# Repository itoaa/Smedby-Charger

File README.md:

Smedby-Charger
==============

Arduino based battery charger

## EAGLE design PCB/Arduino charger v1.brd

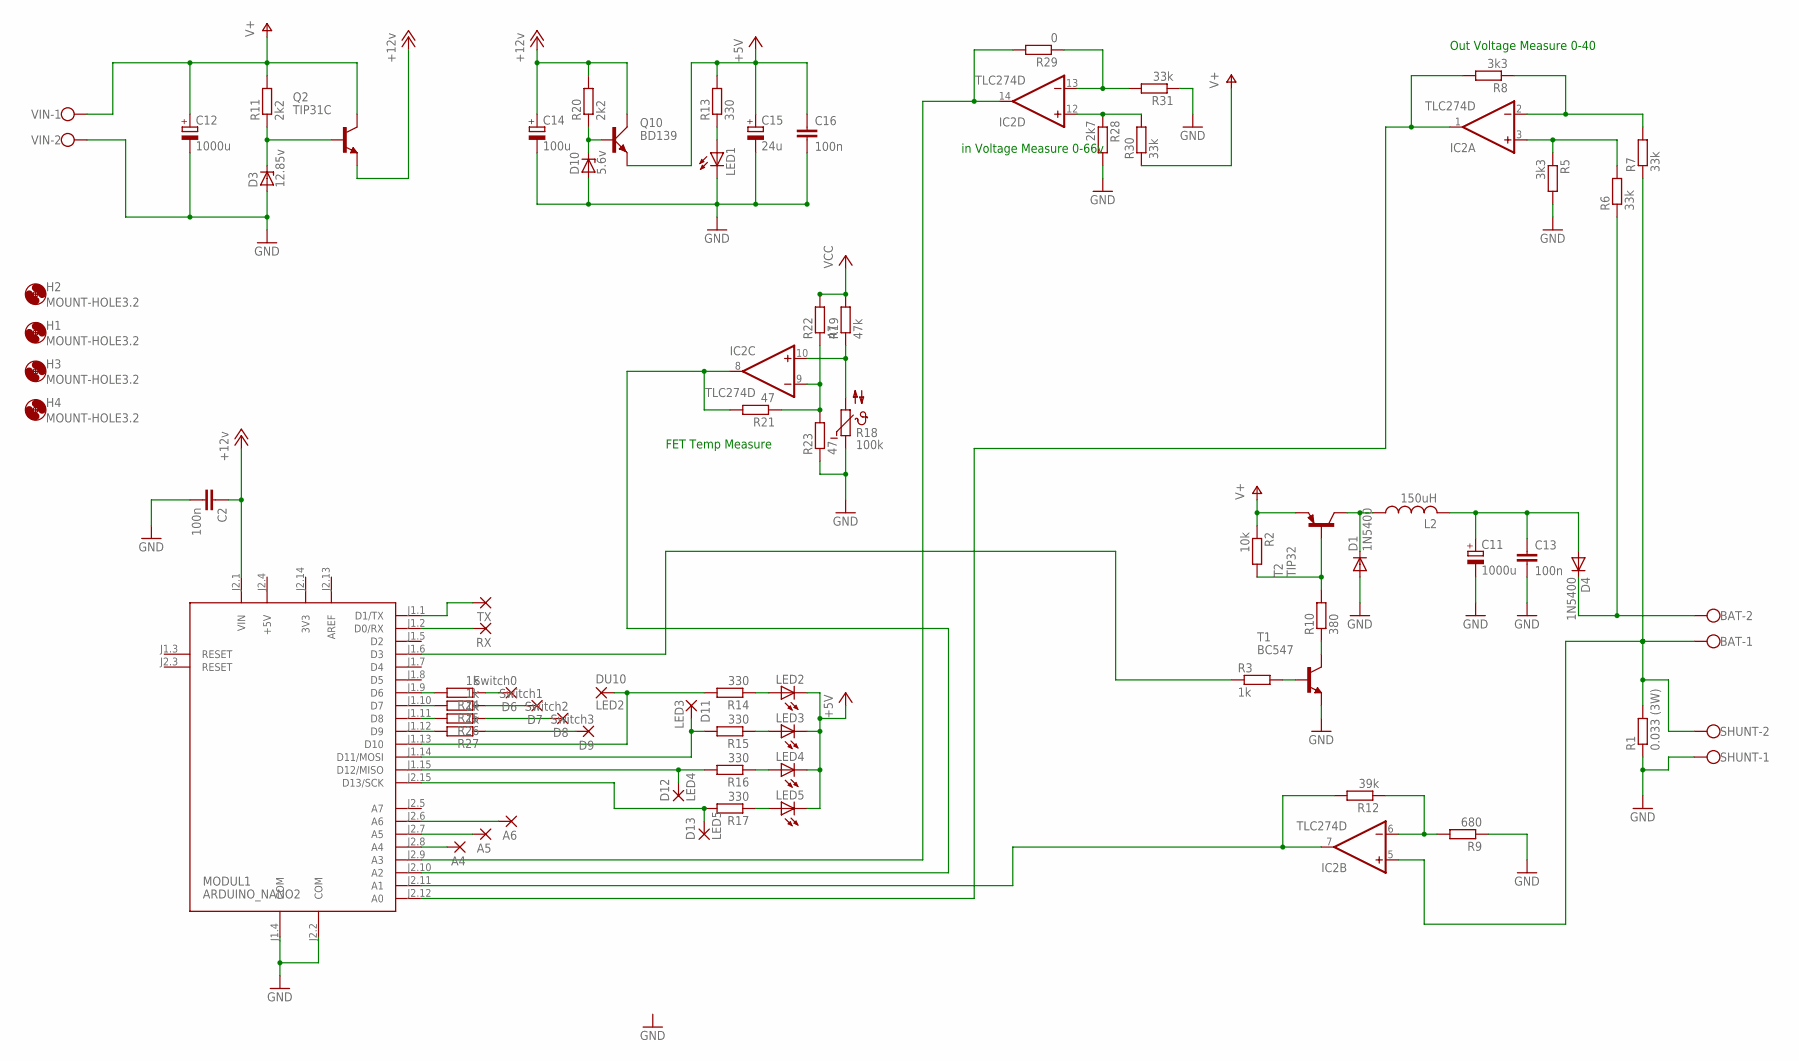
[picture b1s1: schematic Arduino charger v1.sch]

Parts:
A4, A5, A6: 1,6/0,9
BAT: W237-102
C2, C13, C16: 100n; C050-024X044
C11, C12: 1000u; E7,5-18
C14: 100u; E2,5-5
C15: 24u; E2,5-5
D1, D4: 1N5400; DO201-15
D3: 12.85v; DO35Z10
D6: Switch0; 1,6/0,9
D7: Switch1; 1,6/0,9
D8: Switch2; 1,6/0,9
D9: Switch3; 1,6/0,9
D10: 5.6v; DO35Z10
D11: LED3; 1,6/0,9
D12: LED4; 1,6/0,9
D13: LED5; 1,6/0,9
DU10: LED2; 1,6/0,9
H1, H2, H3, H4: MOUNT-HOLE3.2; 3,2
IC2: TLC274D; SO14
L2: 150uH; TJ4-U1
LED1, LED2, LED3, LED4, LED5: LED3MM
MODUL1: ARDUINO_NANO2
Q2: TIP31C; TO220
Q10: BD139; TO126AV
R1: 0.033 (3W); 0922/22
R2: 10k; 0207/2V
R3, R24, R25, R26, R27: 1k; 0207/2V
R5, R8: 3k3; 0207/2V
R6, R7, R30, R31: 33k; 0207/2V
R9: 680; 0207/2V
R10: 380; P0613V
R11: 2k2; 0617/17
R12: 39k; 0207/2V
R13, R14, R15, R16, R17: 330; 0207/2V
R18: 100k; N640
R19: 47k; 0207/2V
R20: 2k2; 0207/2V
R21, R22, R23: 47; 0207/2V
R28: 2k7; 0207/2V
R29: 0; 0207/2V
RX: 1,6/0,9
SHUNT: W237-102
T1: BC547; TO92
T2: TIP32; TO220
TX: 1,6/0,9
VIN: W237-102

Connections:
3V3: MODUL1.J2.14 (3V3)
+5V: C15.+, C16.1, LED2.K (C), LED3.K (C), LED4.K (C), LED5.K (C), MODUL1.J2.4 (+5V), Q10.E, R13.2
+12V: C2.1, C14.+, MODUL1.J2.1 (VIN), Q2.3 (E), Q10.C, R20.2
AREF: MODUL1.J2.13 (AREF)
B+: BAT.2, D4.C, R6.1
B-: BAT.1, IC2.5 (+IN), R1.2, R7.1, SHUNT.2
GND: C2.2, C11.-, C12.-, C13.2, C14.-, C15.-, C16.2, D1.A, D3.A, D10.A, LED1.K (C), MODUL1.J1.4 (COM), MODUL1.J2.2 (COM), R1.1, R5.2, R9.1, R18.1, R23.1, R28.2, R31.1, SHUNT.1, T1.1 (E), VIN.2
unnamed: D3.C, Q2.1 (B), R11.1
unnamed: D1.C, L2.1, T2.2 (C)
unnamed: IC2.12 (+IN), R28.1, R30.2
unnamed: MODUL1.J1.6 (D3), R3.1
unnamed: A4.1, MODUL1.J2.8 (A4)
unnamed: MODUL1.J1.1 (D1/TX), TX.1
unnamed: D10.C, Q10.B, R20.1
unnamed: MODUL1.J1.9 (D6), R24.2
unnamed: R3.2, T1.2 (B)
unnamed: R10.1, T1.3 (C)
unnamed: IC2.6 (-IN), R9.2, R12.1
unnamed: MODUL1.J1.10 (D7), R25.2
unnamed: MODUL1.J1.11 (D8), R26.2
unnamed: MODUL1.J1.12 (D9), R27.2
unnamed: A5.1, MODUL1.J2.7 (A5)
unnamed: A6.1, MODUL1.J2.6 (A6)
unnamed: MODUL1.J1.2 (D0/RX), RX.1
unnamed: C11.+, C13.1, D4.A, L2.2
unnamed: D13.1, MODUL1.J2.15 (D13/SCK), R17.2
unnamed: D12.1, MODUL1.J1.15 (D12/MISO), R16.2
unnamed: R2.2, R10.2, T2.1 (B)
unnamed: IC2.3 (+IN), R5.1, R6.2
unnamed: IC2.7 (OUT), MODUL1.J2.11 (A1), R12.2
unnamed: IC2.2 (-IN), R7.2, R8.1
unnamed: IC2.1 (OUT), MODUL1.J2.12 (A0), R8.2
unnamed: LED1.A, R13.1
unnamed: LED2.A, R14.1
unnamed: LED3.A, R15.1
unnamed: IC2.8 (OUT), MODUL1.J2.10 (A2), R21.2
unnamed: LED4.A, R16.1
unnamed: LED5.A, R17.1
unnamed: IC2.9 (-IN), R21.1, R22.1, R23.2
unnamed: DU10.1, MODUL1.J1.13 (D10), R14.2
unnamed: D11.1, MODUL1.J1.14 (D11/MOSI), R15.2
unnamed: IC2.10 (+IN), R18.2, R19.1
unnamed: IC2.13 (-IN), R29.1, R31.2
unnamed: IC2.14 (OUT), MODUL1.J2.9 (A3), R29.2
unnamed: D6.1, R24.1
unnamed: D7.1, R25.1
unnamed: D8.1, R26.1
unnamed: D9.1, R27.1
V+: C12.+, IC2.4 (V+), Q2.2 (C), R2.1, R11.2, R30.1, T2.3 (E), VIN.1
V-: IC2.11 (V-)
VCC: R19.2, R22.2

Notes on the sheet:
Out Voltage Measure 0-40
FET Temp Measure
in Voltage Measure 0-66v

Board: 2 copper layers, 73 parts (0 on the bottom side), 48 nets, no tracks yet.

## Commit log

2014-05-09 First commit, add one file
2014-05-09 Första commit-försöket med smedbycharger 0.7
2014-05-09 Första commit-försöket med lite proto 0.7 filer
2014-05-09 PCB Added
2014-05-10 removed old .svn stuff
2014-05-10 .svn stuff removesd
2014-05-10 Lonview charger initile added
2014-05-12 Uppdated PCB
2014-05-12 Simplifyed PCB with only real mosfet-driver, no charge-pump, 7805 as 5v regulator mm.
2014-05-19 PCB changes
